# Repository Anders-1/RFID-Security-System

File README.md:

# RFID-Security-System
An RFID Security System based on the Raspberry Pi Pico (revised from the Zero to Pico).

Version History:

<!-- If you put two spaces after a line it makes a new line but not as big 🤷 -->

V1. RPi Zero  
V2. RPi Pico  
  
V3. :shipit: :trollface: :octocat:  

### [CODE](/main.py)

[Tutorial 1](https://littlebirdelectronics.com.au/guides/181/nfc-module-with-raspberry-pi)

[Tutorial 2](https://learn.adafruit.com/adafruit-nfc-rfid-on-raspberry-pi/testing-it-out)

[Tutorial 3](https://core-electronics.com.au/guides/piicodev-rfid-module-guide-for-raspberry-pi/)

[Tutorial 4](http://wiki.sunfounder.cc/index.php?title=PN532_NFC_Module_for_Raspberry_Pi) (with pinout!!!)

[Tutorial 5](https://www.waveshare.com/w/upload/8/83/Nfc-tools_reference_manual.pdf) (reference manual; scroll down)

TODO: 

- [X] Add green light

- [ ] Add startup checker (with beeps and stuff)

- [ ] Document what lights and beeps mean

- [ ] Email when alarm goes off

- [ ] Check todo list in the code too

> [!NOTE]
> This design also works with RPi Zero

Pinout:

| **PN532 NFC RFID Reader** | **Raspberry Pi** |
| --- | --- |
| 5V                        | 5V               |
| GND                       | GND              |
| RX                        | UART TX          |
| TX                        | UART RX          |

| **Breadboard**                   | **Raspberry Pi**      |
| -------------------------------- | --------------------- |
| Button                           | GND, GPIO 23          |
| Button 2 (external?)             | GND, GPIO 25          |
| Red LED                          | 220 Ohm resistor, GND |
| 220 Ohm Resistor (for red led)   | Red LED, GPIO 17      |
| Green LED                        | 220 Ohm resistor, GND |
| 220 Ohm Resistor (for green led) | Green LED, GPIO 24    |
| Door Sensor                      | GND, GPIO 22          |
| Buzzer                           | GND, GPIO 27          |

Prices:

| Name | Price (totals ignore “other”s) |
| --- | --- |
| [RFID Tag](https://www.adafruit.com/product/4033) | $2.95 |
| [(other) Pi Cobbler](https://www.adafruit.com/product/2029) | $6.95 |
| [(other) RFID Controller](https://www.adafruit.com/product/364) | $39.95 |
| [(other) RFID Controller](https://www.amazon.com/dp/B01I1J17LC) | $8.69 |
| [(other) RFID Controller](https://www.amazon.com/HiLetgo-RFID-Kit-Arduino-Raspberry/dp/B01CSTW0IA/ref=sr_1_1_sspa?keywords=rc522+rfid+reader\&linkCode=ll2\&linkId=5c768527322a93c3f1ae3883817b8d14\&qid=1661434446\&s=electronics\&sr=1-1-spons\&psc=1\&spLa=ZW5jcnlwdGVkUXVhbGlmaWVyPUFUWDZGRjdQR01aVzEmZW5jcnlwdGVkSWQ9QTA5OTEzNDNVQjBDOTlMNVlTSEkmZW5jcnlwdGVkQWRJZD1BMDAxMjEzNzNNTEVBRUszQTlRS0cmd2lkZ2V0TmFtZT1zcF9hdGYmYWN0aW9uPWNsaWNrUmVkaXJlY3QmZG9Ob3RMb2dDbGljaz10cnVl) | $5.49 |
| [RFID Controller](https://www.ebay.com/itm/381374529898) | $7.88 |
| [Jumper Wires](https://www.adafruit.com/product/1956) | $3.95 |
| [Breadboard](https://www.adafruit.com/product/4539) | $5.00 |
| [Buzzer](https://www.adafruit.com/product/160) | $1.50 |
| [Magnetic Door Switch](https://www.adafruit.com/product/375) | $3.95 |
| [(other) Pi 4 Model B](https://www.pishop.us/product/raspberry-pi-4-model-b-2gb/?src=raspberrypi) | $45.00 |
| [(other) Resistor Pack](https://www.amazon.com/Elegoo-Values-Resistor-Assortment-Ohm-1M/dp/B072BL2VX1) | $11.99 |
| [(other) Resistors + Others Pack](https://www.amazon.com/Smraza-Breadboard-Resistors-Mega2560-Raspberry/dp/B01HRR7EBG) | $12.69 |
| **Total** | **$25.23** |
| _other_| |
| **Grand Total** | **$25.23** |

Getting the pack saves $8.45

I could get the pack and also get Jumper Wires for $3.95, I could get to tinkering earlier.

I could get the pack and get all the other products, $10.45 more expensive than just getting the pack.

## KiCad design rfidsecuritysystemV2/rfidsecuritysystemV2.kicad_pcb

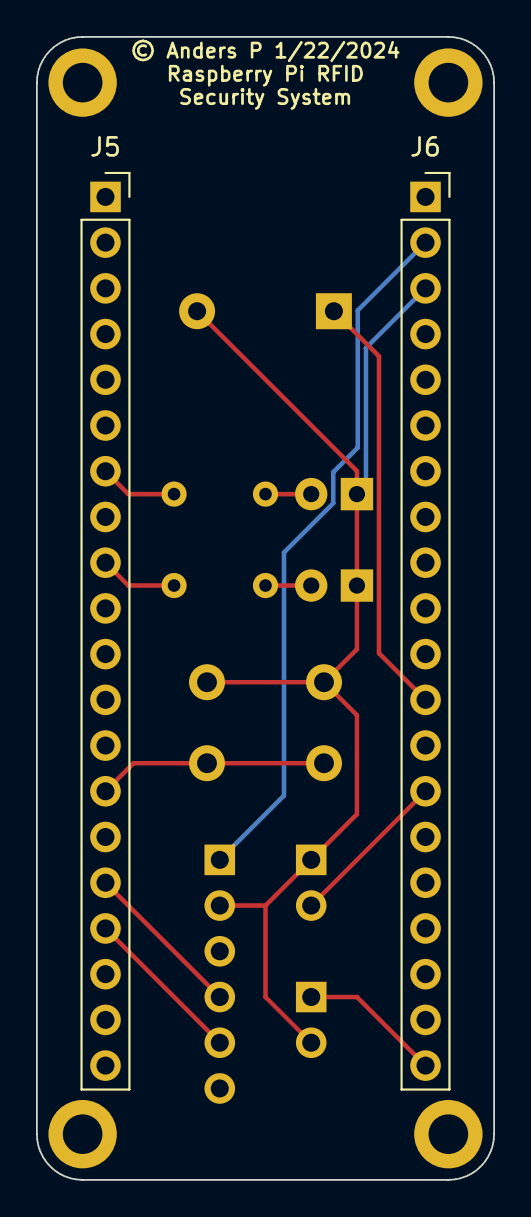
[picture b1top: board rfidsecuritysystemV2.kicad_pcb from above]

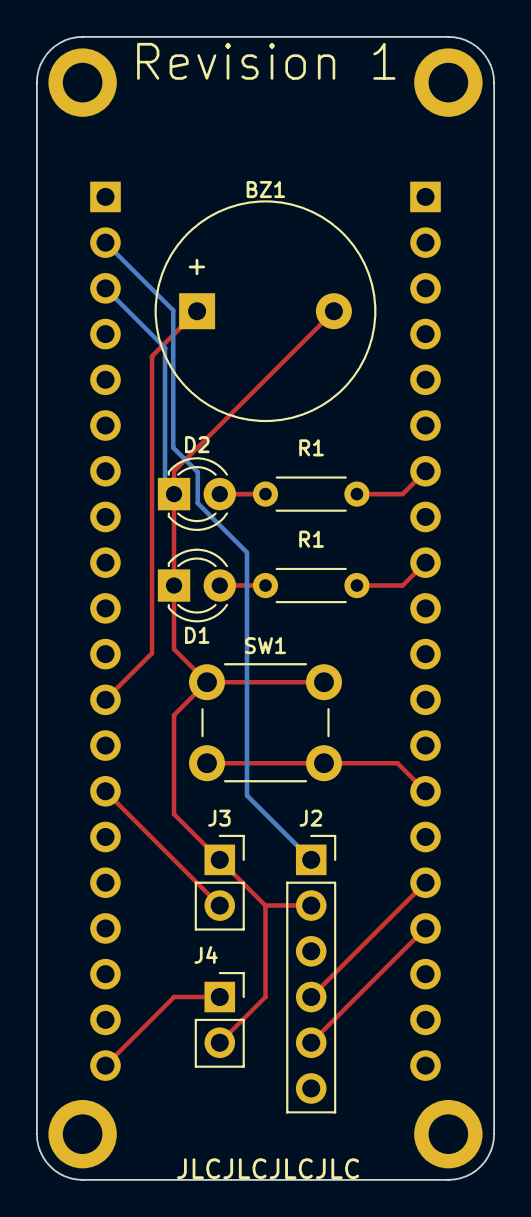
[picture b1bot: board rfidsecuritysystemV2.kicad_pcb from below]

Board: 2 copper layers, 25.4 x 63.5 mm, 15 parts (9 on the bottom side), 12 nets.

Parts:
BZ1: Buzzer; Buzzer_12x9.5RM7.6
D1, D2: LED; LED_D3.0mm
H1, H2, H3, H4: MountingHole; MountingHole_2.2mm_M2_DIN965_Pad
J2: Conn_01x06_Socket; PinSocket_1x06_P2.54mm_Vertical
J3, J4: Conn_01x02_Socket; PinSocket_1x02_P2.54mm_Vertical
J5, J6: Conn_01x20_Socket; PinSocket_1x20_P2.54mm_Vertical
R1, R2: R; R_Axial_DIN0204_L3.6mm_D1.6mm_P5.08mm_Horizontal
SW1: SW_Push; SW_PUSH_6mm

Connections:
+5V: J2.1, J6.2
/GPIO 5: J5.7, R2.2
/GPIO 6: J5.9, R1.2
/GPIO 10: J5.14, SW1.2
/GPIO 16: J4.1, J6.20
/GPIO 21: J3.2, J6.14
/GPIO 22: BZ1.1 (-), J6.12
/UART RX: J2.5, J5.17
/UART TX: J2.4, J5.16
GND: BZ1.2 (+), D1.1 (K), D2.1 (K), J2.2, J3.1, J4.2, J6.3, SW1.1
unnamed: D1.2 (A), R1.1
unnamed: D2.2 (A), R2.1

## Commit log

2024-01-22 add main.py
2024-01-22 move image to images
2024-01-22 add image or smth
2024-01-23 finish v2

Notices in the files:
rfidsecuritysystemV2/rfidsecuritysystemV2.kicad_pcb:
© Anders P 1/22/2024
